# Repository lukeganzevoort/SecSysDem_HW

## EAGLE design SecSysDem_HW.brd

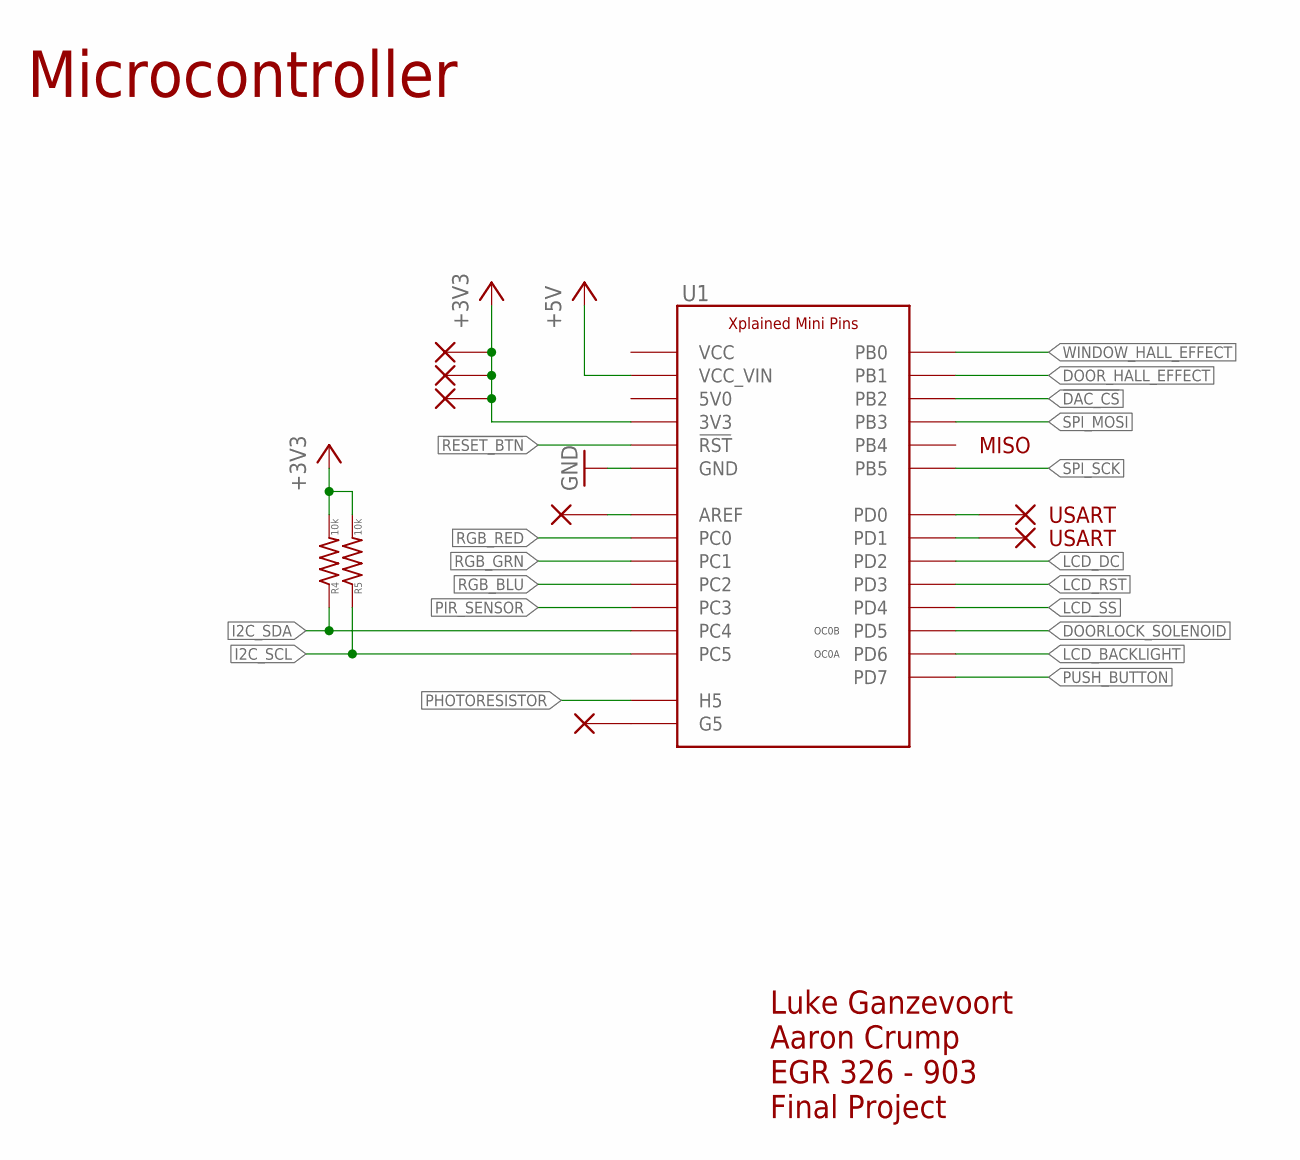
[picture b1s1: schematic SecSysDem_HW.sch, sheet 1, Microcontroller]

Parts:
R4, R5: 10k; C0805
U1: XPLAINED_MINI_PINOUT; XPLAINED_MINI_PINS
V3: TXD; VIA1
V4: RXD; VIA1
V5: G5; VIA1
V6: AREF; VIA1
V7, V8, V9: 3v3; VIA1

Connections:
!DAC_CS: U1.P$25 (PB2); also elsewhere on the board
!RESET_BTN: U1.P$12 (!RST); also elsewhere on the board
+3V3: R4.2, R5.2, U1.P$11 (3V3), V7.P$1, V8.P$1, V9.P$1; also elsewhere on the board
+5V: U1.P$7 (VCC_VIN); also elsewhere on the board
DOORLOCK_SOLENOID: U1.P$20 (PD5); also elsewhere on the board
DOOR_HALL_EFFECT: U1.P$24 (PB1); also elsewhere on the board
GND: U1.P$8 (GND), U1.P$9 (GND), U1.P$29 (GND); also elsewhere on the board
I2C_SCL: R5.1, U1.P$1 (PC5), U1.P$32 (PC5); also elsewhere on the board
I2C_SDA: R4.1, U1.P$2 (PC4), U1.P$31 (PC4); also elsewhere on the board
LCD_BACKLIGHT: U1.P$21 (PD6); also elsewhere on the board
LCD_DC: U1.P$17 (PD2); also elsewhere on the board
LCD_RST: U1.P$18 (PD3); also elsewhere on the board
LCD_SS: U1.P$19 (PD4); also elsewhere on the board
unnamed: U1.P$15 (PD0), V3.P$1
unnamed: U1.P$16 (PD1), V4.P$1
unnamed: U1.P$34 (G5), V5.P$1
unnamed: U1.P$30 (AREF), V6.P$1
PHOTORESISTOR: U1.P$33 (H5); also elsewhere on the board
PIR_SENSOR: U1.P$3 (PC3); also elsewhere on the board
PUSH_BUTTON: U1.P$22 (PD7); also elsewhere on the board
RGB_BLU: U1.P$4 (PC2); also elsewhere on the board
RGB_GRN: U1.P$5 (PC1); also elsewhere on the board
RGB_RED: U1.P$6 (PC0); also elsewhere on the board
SPI_MOSI: U1.P$26 (PB3); also elsewhere on the board
SPI_SCK: U1.P$28 (PB5); also elsewhere on the board
WINDOW_HALL_EFFECT: U1.P$23 (PB0); also elsewhere on the board

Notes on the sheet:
Luke Ganzevoort Aaron Crump EGR 326 - 903 Final Project
USART
MISO
OC0B
OC0A
Microcontroller

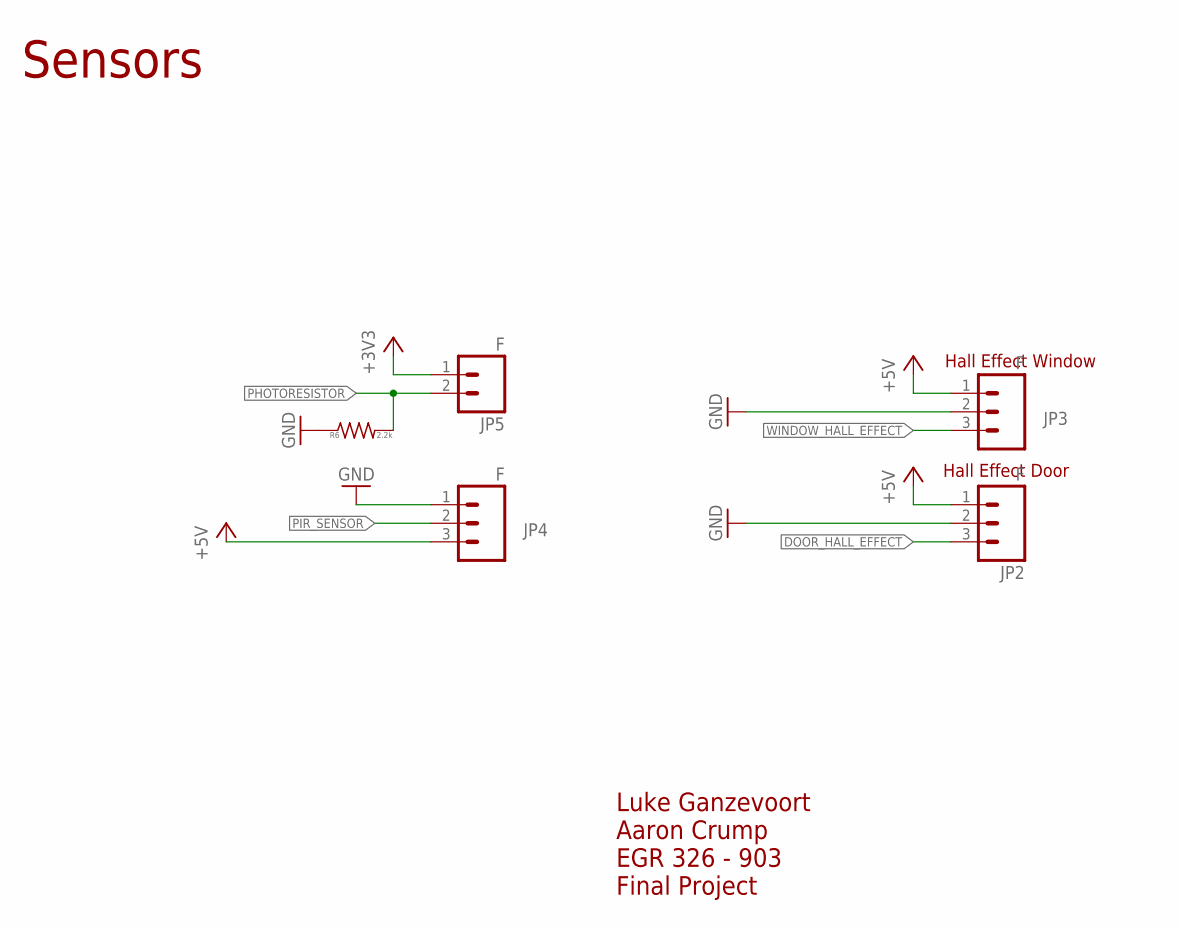
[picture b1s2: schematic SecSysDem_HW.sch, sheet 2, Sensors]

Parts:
JP2, JP3, JP4: F; 1X03
JP5: F; 1X02
R6: 2.2k; C0805

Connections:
+3V3: JP5.1; also elsewhere on the board
+5V: JP2.1, JP3.1, JP4.3; also elsewhere on the board
DOOR_HALL_EFFECT: JP2.3; also elsewhere on the board
GND: JP2.2, JP3.2, JP4.1, R6.1; also elsewhere on the board
PHOTORESISTOR: JP5.2, R6.2; also elsewhere on the board
PIR_SENSOR: JP4.2; also elsewhere on the board
WINDOW_HALL_EFFECT: JP3.3; also elsewhere on the board

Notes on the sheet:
Hall Effect Window
Hall Effect Door
Luke Ganzevoort Aaron Crump EGR 326 - 903 Final Project
Sensors

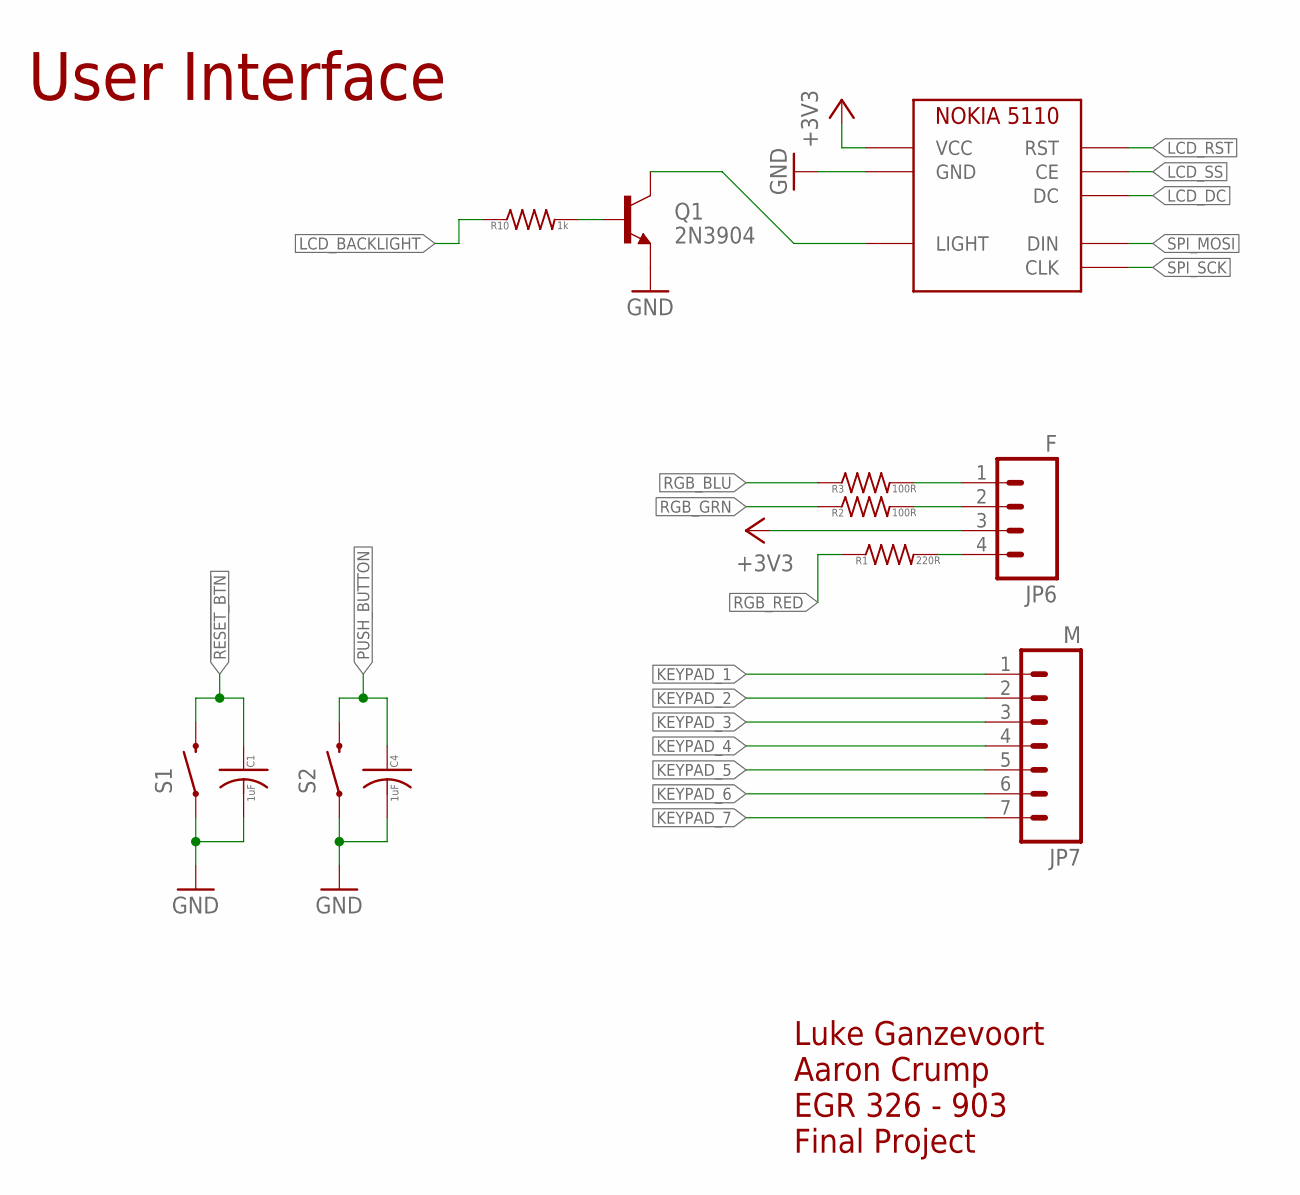
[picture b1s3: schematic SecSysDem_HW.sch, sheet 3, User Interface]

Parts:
C1, C4: 1uF; C0805
JP6: F; 1X04
JP7: M; 1X07
Q1: 2N3904; TO-92-AMMO
R1: 220R; C0805
R2, R3: 100R; C0805
R10: 1k; C0805
S1, S2: TACTILE_SWITCHTHROUGH_HOLE; TACTILE_SWITCH
U$3: NOKIA_5110_LCD; NOKIA_5110

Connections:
!RESET_BTN: C1.1 (POS), S1.3 (2), S1.4 (2); also elsewhere on the board
+3V3: JP6.3, U$3.P$6 (VCC), U$3.P$14 (VCC); also elsewhere on the board
GND: C1.2 (NEG), C4.2 (NEG), Q1.3 (E), S1.1, S1.2 (1), S2.1, S2.2 (1), U$3.P$8 (GND), U$3.P$16 (GND); also elsewhere on the board
KEYPAD_1: JP7.1; also elsewhere on the board
KEYPAD_2: JP7.2; also elsewhere on the board
KEYPAD_3: JP7.3; also elsewhere on the board
KEYPAD_4: JP7.4; also elsewhere on the board
KEYPAD_5: JP7.5; also elsewhere on the board
KEYPAD_6: JP7.6; also elsewhere on the board
KEYPAD_7: JP7.7; also elsewhere on the board
LCD_BACKLIGHT: R10.1; also elsewhere on the board
LCD_DC: U$3.P$3 (DC), U$3.P$11 (DC); also elsewhere on the board
LCD_RST: U$3.P$1 (RST), U$3.P$9 (RST); also elsewhere on the board
LCD_SS: U$3.P$2 (CE), U$3.P$10 (CE); also elsewhere on the board
unnamed: JP6.4, R1.2
unnamed: JP6.2, R2.2
unnamed: JP6.1, R3.2
unnamed: Q1.2 (B), R10.2
unnamed: Q1.1 (C), U$3.P$7 (LIGHT), U$3.P$15 (LIGHT)
PUSH_BUTTON: C4.1 (POS), S2.3 (2), S2.4 (2); also elsewhere on the board
RGB_BLU: R3.1; also elsewhere on the board
RGB_GRN: R2.1; also elsewhere on the board
RGB_RED: R1.1; also elsewhere on the board
SPI_MOSI: U$3.P$4 (DIN), U$3.P$12 (DIN); also elsewhere on the board
SPI_SCK: U$3.P$5 (CLK), U$3.P$13 (CLK); also elsewhere on the board

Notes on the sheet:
Luke Ganzevoort Aaron Crump EGR 326 - 903 Final Project
User Interface

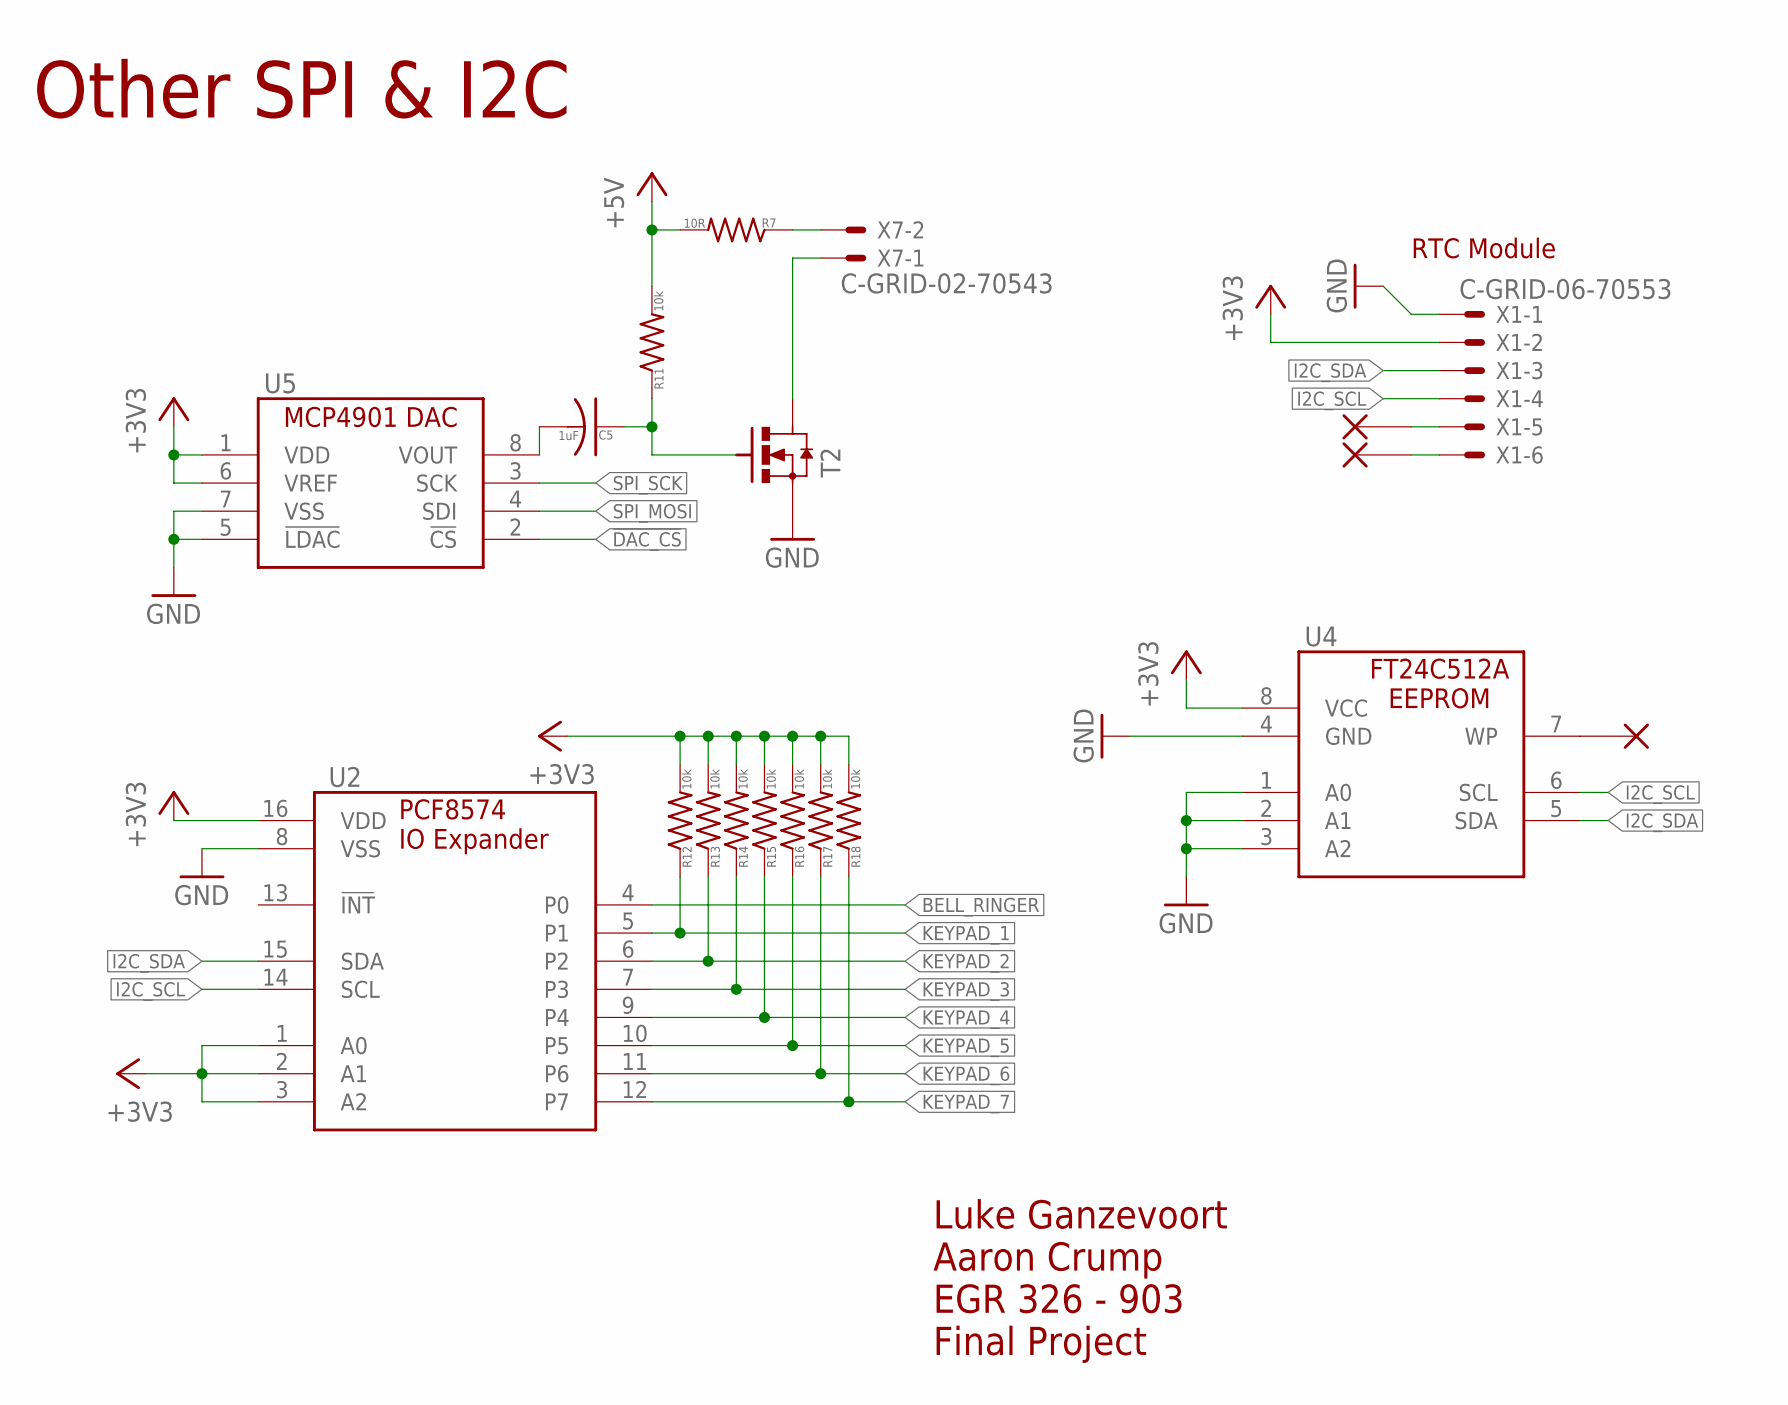
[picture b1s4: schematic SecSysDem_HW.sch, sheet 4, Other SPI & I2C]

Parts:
C5: 1uF; C0805
R7: 10R; C0805
R11, R12, R13, R14, R15, R16, R17, R18: 10k; C0805
T2: MOSFET_NCHANNEL_ENHANCEMENT2N7002,215; SOT23
U2: PCF8574_IO_EXPANDER; DIL16
U4: FT24C512A; 8-SOIC
U5: MCP4901-E/SN; 8-SOIC
V1: WP; VIA1
V2: 32k; VIA1
V10: SQW; VIA1
X1: C-GRID-06-70553; 70553-06
X7: C-GRID-02-70543; 70543-02

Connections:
!DAC_CS: U5.2 (!CS); also elsewhere on the board
+3V3: R12.2, R13.2, R14.2, R15.2, R16.2, R17.2, R18.2, U2.1 (A0), U2.2 (A1), U2.3 (A2), U2.16 (VDD), U4.8 (VCC), U5.1 (VDD), U5.6 (VREF), X1.2; also elsewhere on the board
+5V: R7.2, R11.2; also elsewhere on the board
BELL_RINGER: U2.4 (P0); also elsewhere on the board
GND: T2.2 (S), U2.8 (VSS), U4.1 (A0), U4.2 (A1), U4.3 (A2), U4.4 (GND), U5.5 (!LDAC), U5.7 (VSS), X1.1; also elsewhere on the board
I2C_SCL: U2.14 (SCL), U4.6 (SCL), X1.4; also elsewhere on the board
I2C_SDA: U2.15 (SDA), U4.5 (SDA), X1.3; also elsewhere on the board
KEYPAD_1: R12.1, U2.5 (P1); also elsewhere on the board
KEYPAD_2: R13.1, U2.6 (P2); also elsewhere on the board
KEYPAD_3: R14.1, U2.7 (P3); also elsewhere on the board
KEYPAD_4: R15.1, U2.9 (P4); also elsewhere on the board
KEYPAD_5: R16.1, U2.10 (P5); also elsewhere on the board
KEYPAD_6: R17.1, U2.11 (P6); also elsewhere on the board
KEYPAD_7: R18.1, U2.12 (P7); also elsewhere on the board
unnamed: C5.1 (POS), R11.1, T2.1 (G)
unnamed: T2.3 (D), X7.1
unnamed: U4.7 (WP), V1.P$1
unnamed: R7.1, X7.2
unnamed: V2.P$1, X1.6
unnamed: C5.2 (NEG), U5.8 (VOUT)
unnamed: V10.P$1, X1.5
SPI_MOSI: U5.4 (SDI); also elsewhere on the board
SPI_SCK: U5.3 (SCK); also elsewhere on the board

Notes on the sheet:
RTC Module
Luke Ganzevoort Aaron Crump EGR 326 - 903 Final Project
Other SPI & I2C

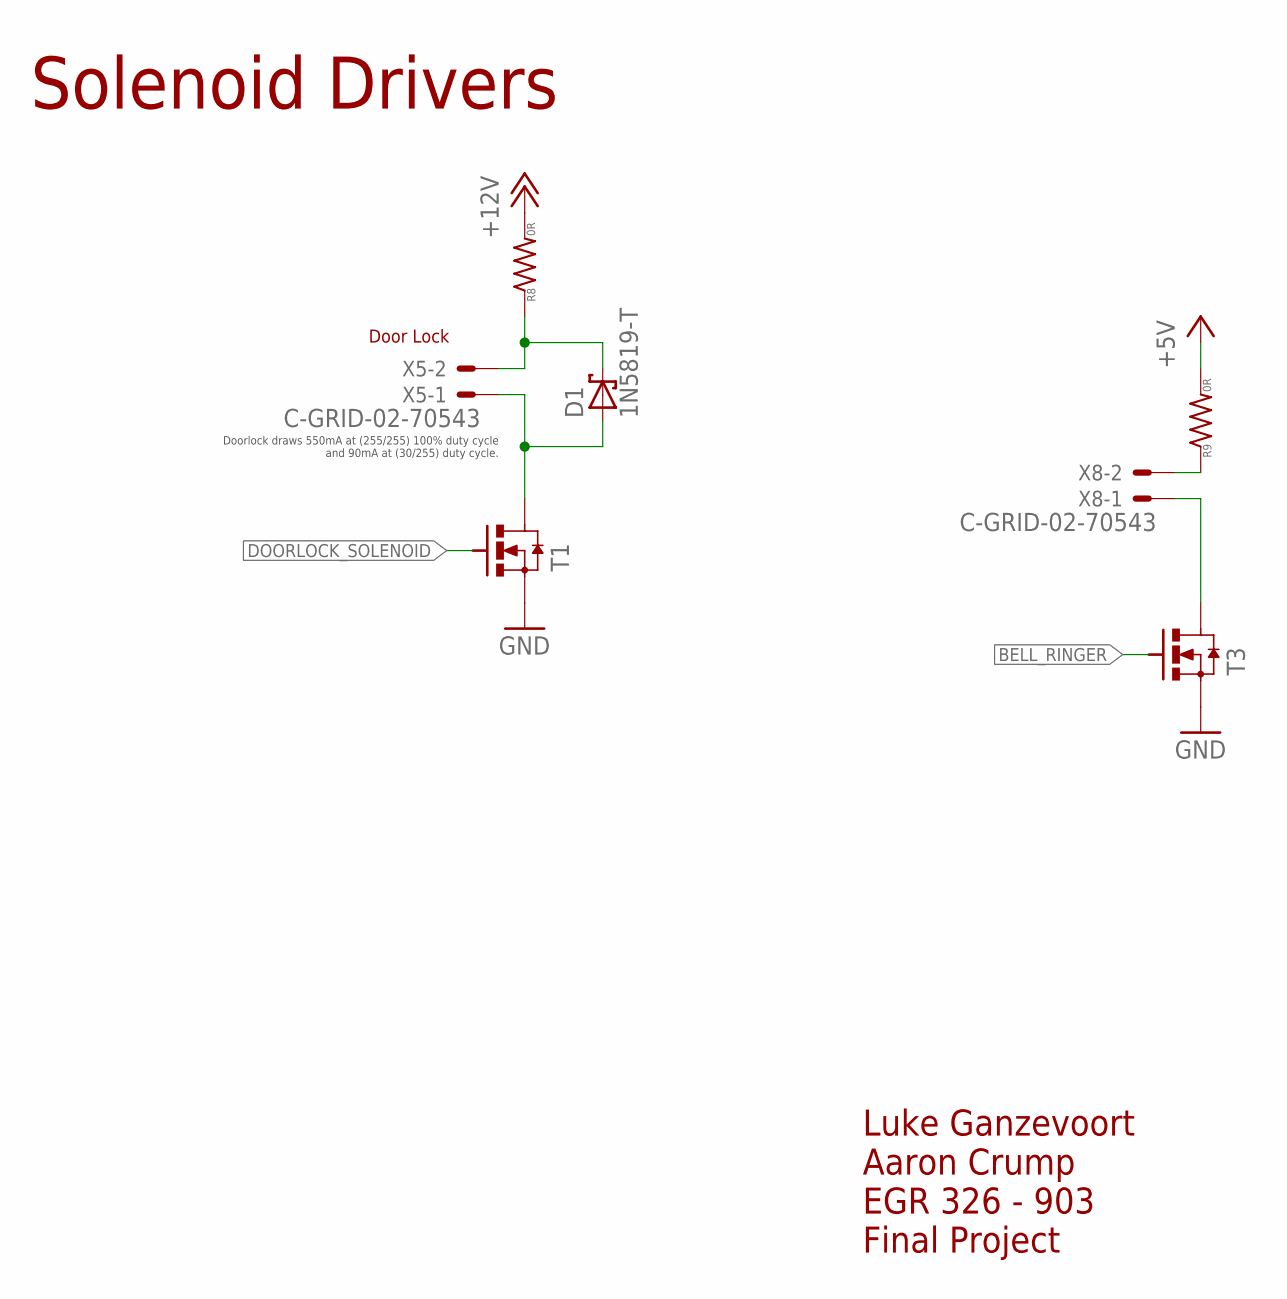
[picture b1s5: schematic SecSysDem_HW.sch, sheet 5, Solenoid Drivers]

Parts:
D1: 1N5819-T; DO41-7.6
R8, R9: 0R; C0805
T1, T3: MOSFET_NCHANNEL_ENHANCEMENT2N7002,215; SOT23
X5, X8: C-GRID-02-70543; 70543-02

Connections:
+5V: R9.2; also elsewhere on the board
+12V: R8.2; also elsewhere on the board
BELL_RINGER: T3.1 (G); also elsewhere on the board
DOORLOCK_SOLENOID: T1.1 (G); also elsewhere on the board
GND: T1.2 (S), T3.2 (S); also elsewhere on the board
unnamed: D1.A, T1.3 (D), X5.1
unnamed: R9.1, X8.2
unnamed: T3.3 (D), X8.1
unnamed: D1.C, R8.1, X5.2

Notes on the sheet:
Door Lock
Doorlock draws 550mA at (255/255) 100% duty cycle and 90mA at (30/255) duty cycle.
Luke Ganzevoort Aaron Crump EGR 326 - 903 Final Project
Solenoid Drivers

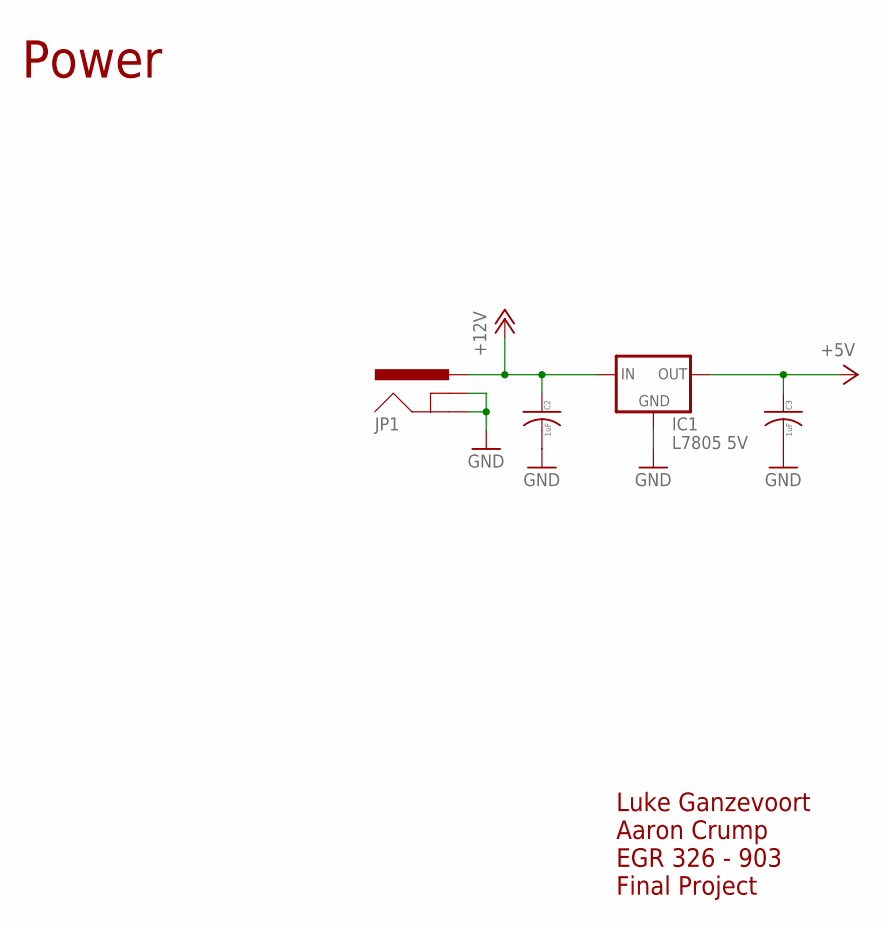
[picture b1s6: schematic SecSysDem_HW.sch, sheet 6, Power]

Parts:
C2, C3: 1uF; C0805
IC1: L7805 5V; 78XXL
JP1: POWER_JACKPTH_BREAD; POWER_JACK_PTH_BREAD

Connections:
+5V: C3.1 (POS), IC1.OUT; also elsewhere on the board
+12V: C2.1 (POS), IC1.IN, JP1.PWR; also elsewhere on the board
GND: C2.2 (NEG), C3.2 (NEG), IC1.GND, JP1.GND, JP1.GNDBREAK; also elsewhere on the board

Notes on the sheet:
Luke Ganzevoort Aaron Crump EGR 326 - 903 Final Project
Power

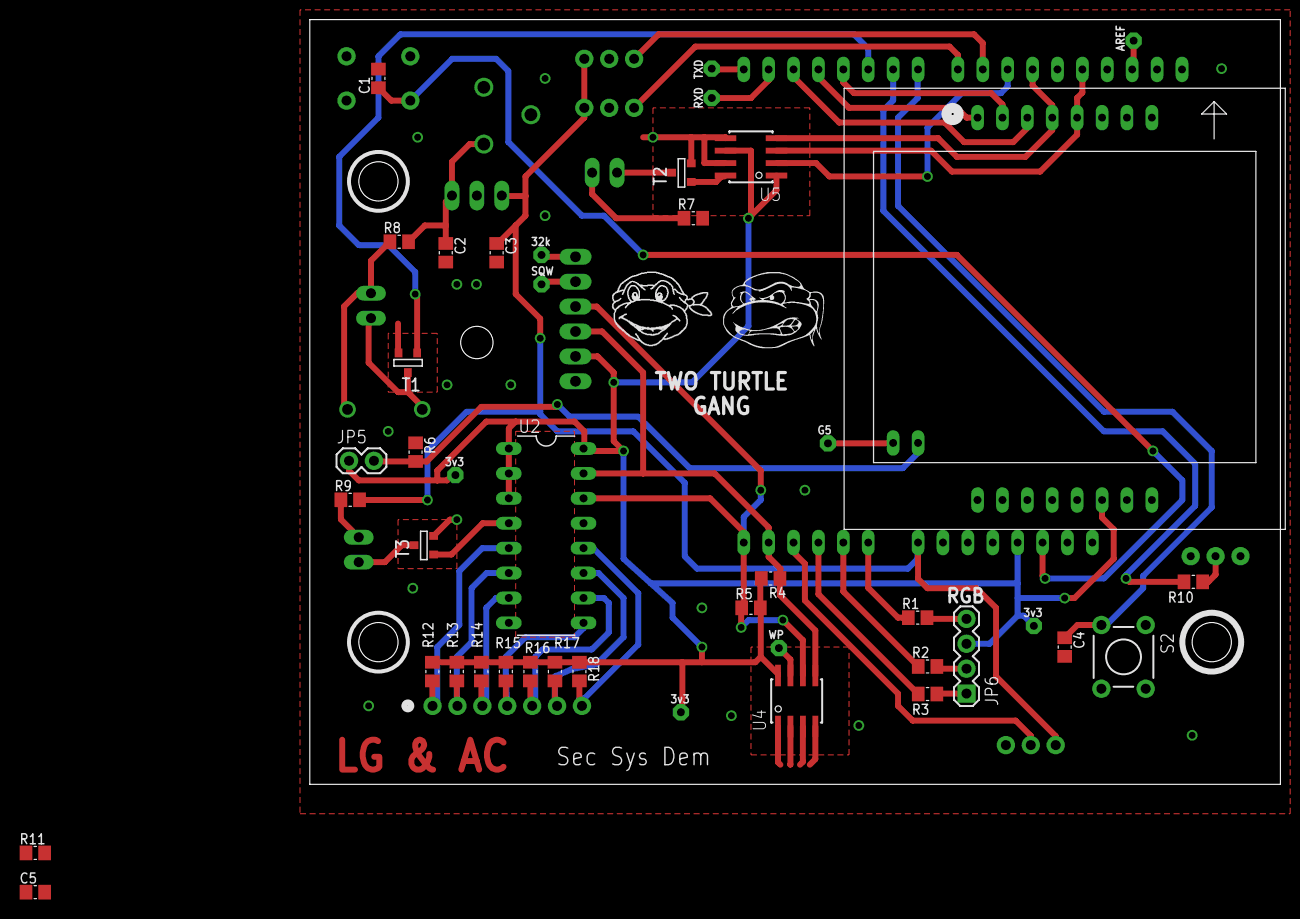
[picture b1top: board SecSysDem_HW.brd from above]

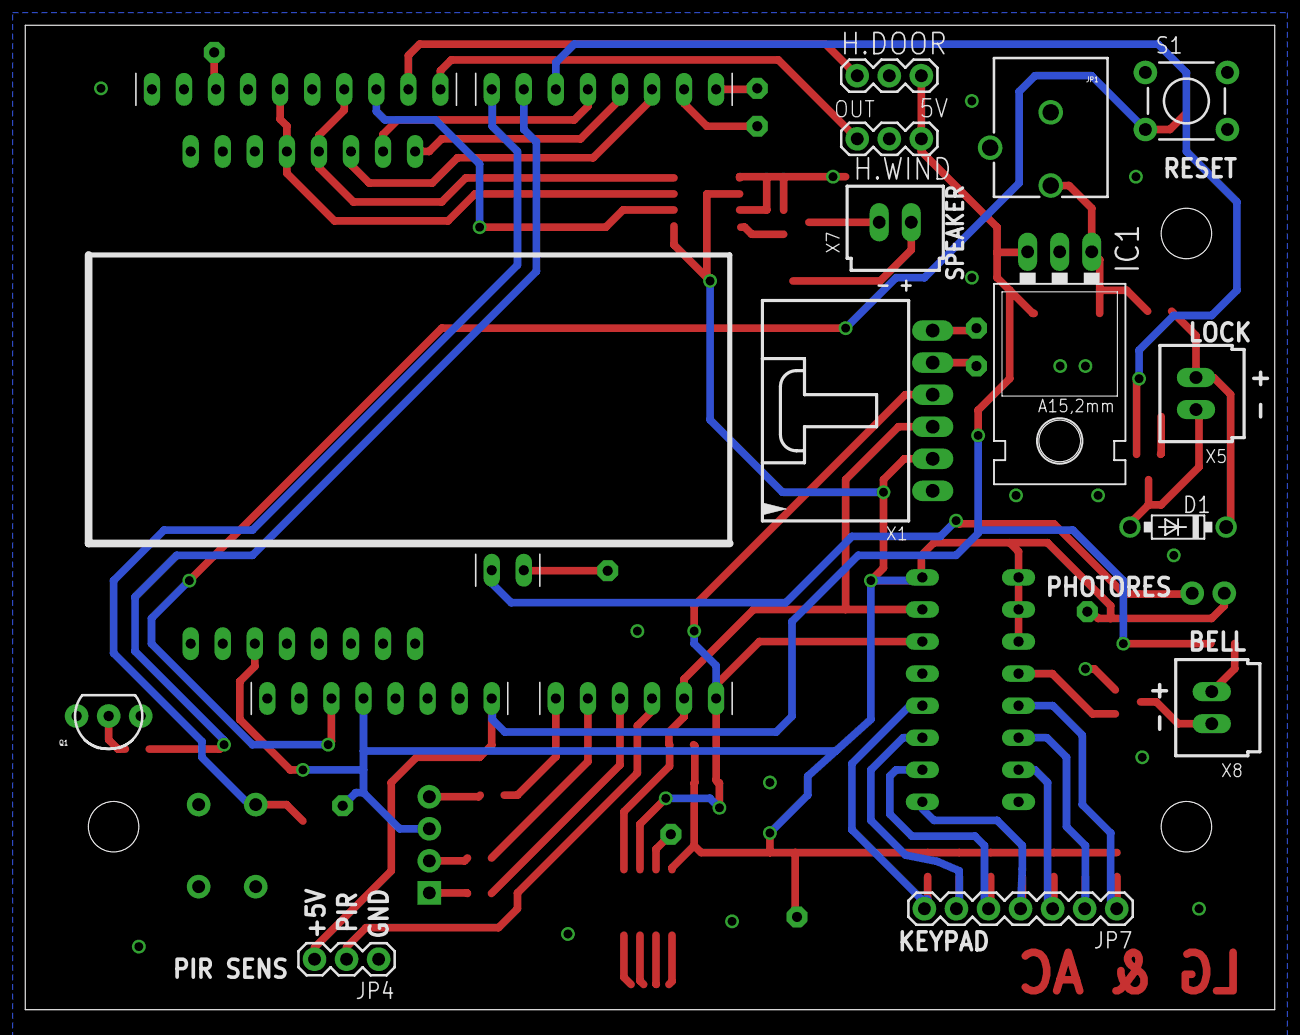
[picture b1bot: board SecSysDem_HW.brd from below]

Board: 2 copper layers, 99.0 x 78.0 mm, 59 parts (14 on the bottom side), 51 nets.

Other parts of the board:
U$1: NINJA_TURTLE1
U$4: NINJA_TURTLE2

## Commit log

2015-10-04 initiated
2015-10-15 Completed schematic
2015-10-15 Added NPN transistor to power the LCD backlight
2015-10-17 removed backup files
2015-10-17 Changed EEPROM address pins (A2, A1, A0) to VCC because of addressing conflicts with the RTC module on board EEPROM.
2015-10-18 Started the pcb layout. PCB made to fit the TaydaElectronics.com plastic box
2015-10-20 Added flyback diode to solenoid. Changed most connectors to verticle. Continued PCB layout and increased PCB size.
2015-10-20 Changed DAC to MCP4901-E/SN because the package was too small.
2015-10-20 Continued board layout. Most components in proper place. No traces yet.
2015-10-20 Continued PCB layout.
2015-10-20 Switched IO expander pins to be keypad pins.
2015-10-21 Continued PCB layout. Moved some pin options.
2015-10-21 Finished PCB layout.
2015-10-21 Refinished board layout with silkscreen.
2015-10-22 Change bell to +5v
2015-10-27 Changed the pins so that the backlight is on PD6 instead of PD7 for pwm.
2015-10-27 Added to ignore gerber files
2015-12-03 Added text
2015-12-03 Made board mods to schematic
2015-12-10 Changed schematic into several pages
2015-12-11 Revert "Update .gitignore"
    This reverts commit 8e6eb89def572076a2fd92689a9dd7e37aad7c03.
2015-12-11 Revert "Added to ignore gerber files"
    This reverts commit fd6e0030c171279b04e2095d4b50efb3de748108.
2015-12-11 Revert "initiated"
    This reverts commit 96e71088ff959b18f05efe8bc4a541e1ee05d8f5.

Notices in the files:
parts and their libraries:
SparkFun-Connectors: Licensing: Creative Commons ShareAlike 4.0 International - https://creativecommons.org/licenses/by-sa/4.0
